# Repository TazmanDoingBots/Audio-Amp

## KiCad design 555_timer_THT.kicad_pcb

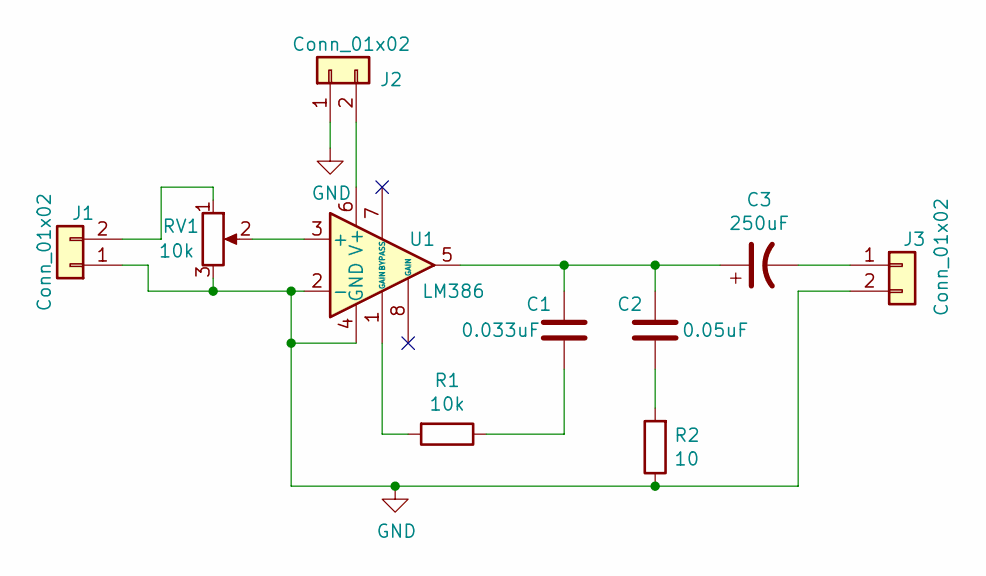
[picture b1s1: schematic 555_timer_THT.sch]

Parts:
C1: 0.033uF; C_1812_4532Metric_Pad1.57x3.40mm_HandSolder
C2: 0.05uF; C_1206_3216Metric_Pad1.33x1.80mm_HandSolder
C3: 250uF; CP_Axial_L38.0mm_D18.0mm_P44.00mm_Horizontal
J1, J2, J3: Conn_01x02; PinHeader_1x02_P2.54mm_Vertical
R1: 10k; R_Axial_DIN0207_L6.3mm_D2.5mm_P2.54mm_Vertical
R2: 10; R_Axial_DIN0207_L6.3mm_D2.5mm_P2.54mm_Vertical
RV1: 10k; Potentiometer_Alps_RK09K_Single_Horizontal
U1: LM386; DIP-8_W7.62mm

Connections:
GND: J1.1, J2.1, J3.2, R2.1, RV1.3, U1.2 (-), U1.4 (GND)
unnamed: C1.1, C2.1, C3.1, U1.5
unnamed: C1.2, R1.1
unnamed: C2.2, R2.2
unnamed: C3.2, J3.1
unnamed: J1.2, RV1.1
unnamed: J2.2, U1.6 (V+)
unnamed: R1.2, U1.1 (GAIN)
unnamed: RV1.2, U1.3 (+)

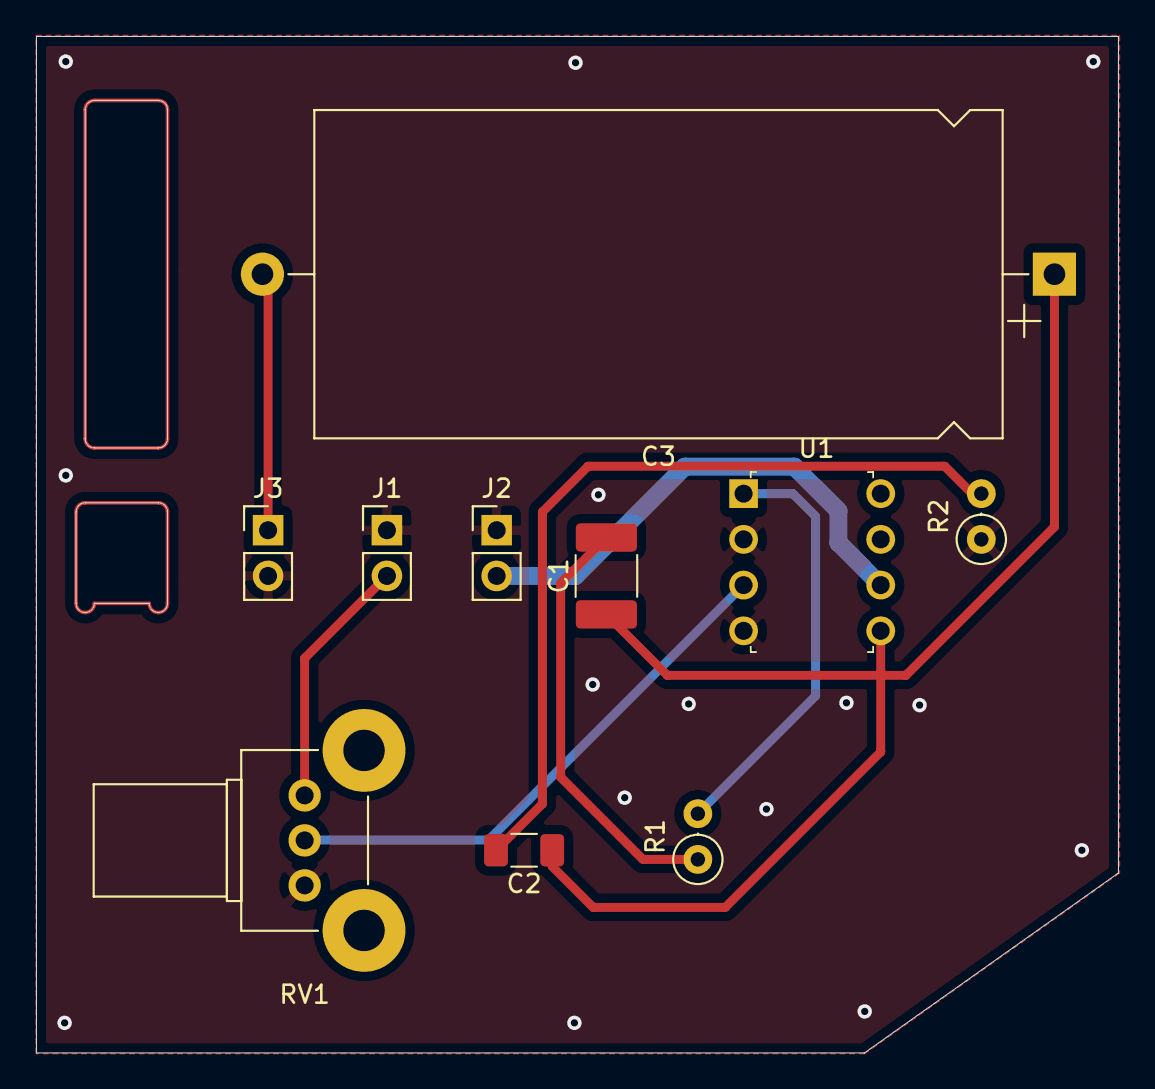
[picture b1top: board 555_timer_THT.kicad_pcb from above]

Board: 2 copper layers, 60.1 x 56.5 mm, 10 parts (0 on the bottom side), 9 nets.

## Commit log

2021-01-03 Pushing for revision and double checking measurements
2021-01-03 Screwed Up naming but these are the rest of the files
2021-01-07 Rename 555_timer_THT.kicad_pcb to AudioAmp.kicad_pcb
2021-01-07 Rename 555_timer_THT.sch to Audio-Amp.sch
2021-01-07 Rename AudioAmp.pro to AudioAmp1.pro
2021-01-08 Edits based on what I see
2021-01-11 Fixed major problems on PCB file
